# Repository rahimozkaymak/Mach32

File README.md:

# Mach32
An ESP32 based rocket flight computer

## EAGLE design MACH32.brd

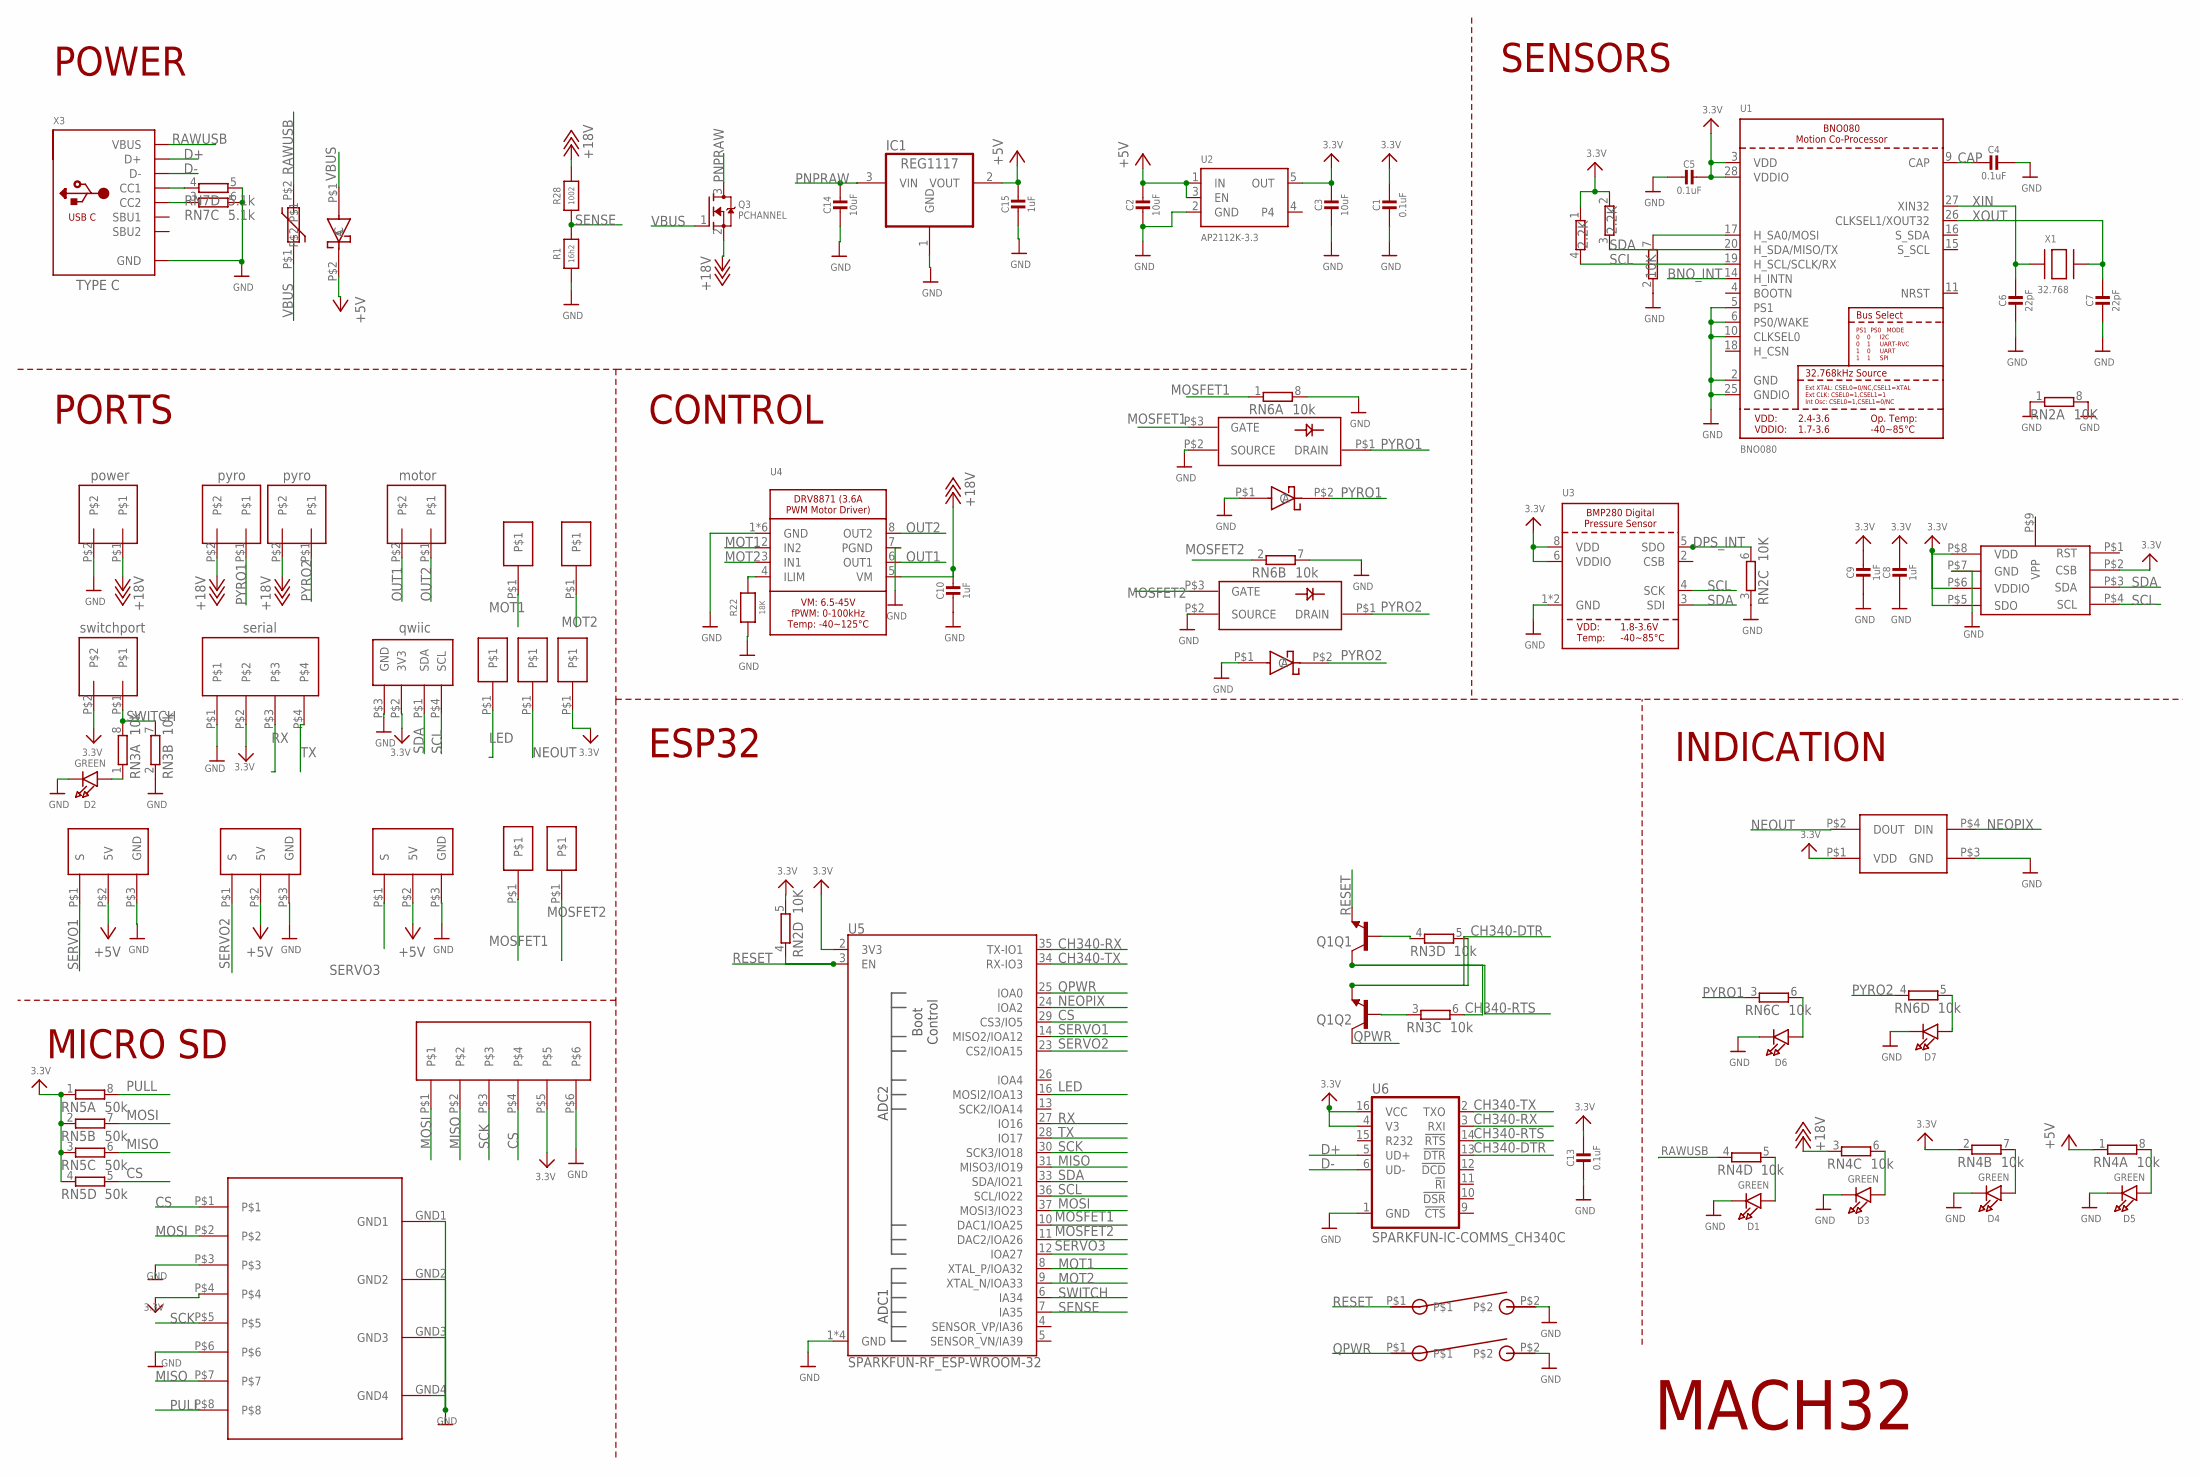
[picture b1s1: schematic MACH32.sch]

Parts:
C1, C4, C5, C13: 0.1uF; 0603-NO
C2, C3, C14: 10uF; 0805-NO
C6, C7: 22pF; 0603-NO
C8, C9, C10, C15: 1uF; 0603-NO
D1, D2, D3, D4, D5, D6, D7: GREEN; CHIPLED_0603_NOOUTLINE
GENERALDIODE, GENERALDIODE2: PG-TSDSON-8-32; BSZ036NE2LSATMA1
IC1: REG1117; SOT223
Q1: SPARKFUN-DISCRETESEMI_TRANS_NPN_DUAL-MBT3904DW1T1; SPARKFUN-DISCRETESEMI_SC70-6
Q3: PCHANNEL; SOT23
R1: 16h2; MICROBUILDER__1206MP
R22: 18K; MICROBUILDER__0603MP
R28: 1002; MICROBUILDER__1206MP
RN1: 2.2K; EXB34V
RN2: 10K; EXB38V
RN3, RN4, RN6: 10k; EXB38V
RN5: 50k; EXB38V
RN7: 5.1k; EXB38V
U1: BNO080
U2: AP2112K-3.3; SOT23-5
U3: BMP280_COMBO; BMX280_COMBO
U4: MICROBUILDER_DRV8871; MICROBUILDER_HSOP8
U5: SPARKFUN-RF_ESP-WROOM-32
U6: SPARKFUN-IC-COMMS_CH340C; SPARKFUN-IC-COMMS_SO016
U$17: 2SMPB-02E; 2021
U$25, U$27, U$28, U$30, U$34: OSTTEXX0104
U$31: DF3-4
U$32: QWIIC; QWIIC_V
U$47: PTC; 1210PTC
U$48, U$49, U$50: SERVO
U$51: SK681-2020; SK6812-2020
U$52, U$53, U$91: SS24FL; XC6220
U$57, U$58, U$59, U$100, U$104, U$105, U$106: MALIPAD
U$67: DF3-6
U$70: ST1W008S4AR1500
U$73, U$74: OMRONSWITCH; BUTTONOMRON
X1: 32.768; XTAL3215
X3: MICROBUILDER_USB_C; MICROBUILDER_USB_C_CUSB31-CFM2AX-01-X

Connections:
3.3V: C1.1, C3.1, C5.1, C8.1, C9.1, C13.1, RN1.1, RN1.2 (1), RN2.5 (2), RN4.2 (1), RN5.1, RN5.2 (1), RN5.3 (1), RN5.4 (1), U1.3 (VDD), U1.28 (VDDIO), U2.5 (OUT), U3.6 (VDDIO), U3.8 (VDD), U5.2 (3V3), U6.4 (V3), U6.16 (VCC), U$17.P$2 (CSB), U$17.P$5 (SDO), U$17.P$6 (VDDIO), U$17.P$8 (VDD), U$31.P$2, U$32.P$2 (3V3), U$34.P$2, U$51.P$1 (VDD), U$57.P$1, U$67.P$5, U$70.P$4
+5V: C2.1, C15.1, IC1.2 (VOUT), RN4.1, U2.1 (IN), U2.3 (EN), U$48.P$2 (5V), U$49.P$2 (5V), U$50.P$2 (5V), U$91.P$2 (C)
+18V: C10.1, Q3.2 (S), R28.2, RN4.3 (1), U4.5 (VM), U$25.P$1, U$27.P$2, U$30.P$2
BNO_INT: U1.14 (H_INTN)
CAP: C4.2, U1.9 (CAP)
CH340-DTR: Q1.1 (E), RN3.5 (2), U6.13 (!DTR)
CH340-RTS: Q1.3 (C), RN3.6 (2), U6.14 (!RTS)
CH340-RX: U5.35 (TX-IO1), U6.3 (RXI)
CH340-TX: U5.34 (RX-IO3), U6.2 (TXO)
CS: RN5.5 (2), U5.29 (CS3/IO5), U$67.P$4, U$70.P$1
D+: U6.5 (UD+), X3.A6 (D+), X3.B6 (D+)
D-: U6.6 (UD-), X3.A7 (D-), X3.B7 (D-)
DPS_INT: RN2.6 (2), U3.5 (SDO)
GND: C1.2, C2.2, C3.2, C4.1, C5.2, C6.2, C7.2, C8.2, C9.2, C10.2, C13.2, C14.2, C15.2, D1.C, D2.C, D3.C, D4.C, D5.C, D6.C, D7.C, GENERALDIODE.P$2 (SOURCE), GENERALDIODE2.P$2 (SOURCE), IC1.1 (GND), R1.1, R22.1, RN2.1, RN2.2 (1), RN2.3 (1), RN2.8 (2), RN3.2 (1), RN6.7 (2), RN6.8 (2), RN7.5 (2), RN7.6 (2), U1.2 (GND), U1.5 (PS1), U1.6 (PS0/WAKE), U1.10 (CLKSEL0), U1.25 (GNDIO), U2.2 (GND), U3.1 (GND), U3.7 (GND), U4.1 (GND), U4.7 (PGND), U4.GND, U4.P$1 (GND), U4.P$2 (GND), U4.P$3 (GND), U4.P$4 (GND), U5.1 (GND), U5.15 (GND), U5.38 (GND), U5.GND, U6.1 (GND), U$17.P$7 (GND), U$25.P$2, U$31.P$1, U$32.P$3 (GND), U$48.P$3 (GND), U$49.P$3 (GND), U$50.P$3 (GND), U$51.P$3 (GND), U$52.P$1 (A), U$53.P$1 (A), U$67.P$6, U$70.GND1, U$70.GND2, U$70.GND3, U$70.GND4, U$70.P$3, U$70.P$6, U$73.P$2, U$74.P$2, X3.A1B12 (GND), X3.B1A12 (GND)
LED: U5.16 (MOSI2/IOA13), U$59.P$1
MISO: RN5.6 (2), U5.31 (MISO3/IO19), U$67.P$2, U$70.P$7
MOSFET1: GENERALDIODE.P$3 (GATE), RN6.1, U5.10 (DAC1/IOA25), U$100.P$1
MOSFET2: GENERALDIODE2.P$3 (GATE), RN6.2 (1), U5.11 (DAC2/IOA26), U$104.P$1
MOSI: RN5.7 (2), U5.37 (MOSI3/IO23), U$67.P$1, U$70.P$2
MOT1: U4.2 (IN2), U5.8 (XTAL_P/IOA32), U$105.P$1
MOT2: U4.3 (IN1), U5.9 (XTAL_N/IOA33), U$106.P$1
unnamed: RN2.7 (2), U1.17 (H_SA0/MOSI)
unnamed: D2.A, RN3.1
unnamed: D1.A, RN4.5 (2)
unnamed: R22.2, U4.4 (ILIM)
unnamed: D3.A, RN4.6 (2)
unnamed: D4.A, RN4.7 (2)
unnamed: D5.A, RN4.8 (2)
unnamed: Q1.5 (B), RN3.4 (1)
unnamed: Q1.2 (B), RN3.3 (1)
unnamed: RN7.4 (1), X3.A5 (CC1)
unnamed: D6.A, RN6.6 (2)
unnamed: D7.A, RN6.5 (2)
unnamed: RN7.3 (1), X3.B5 (CC2)
NEOPIX: U5.24 (IOA2), U$51.P$4 (DIN)
NEOUT: U$51.P$2 (DOUT), U$58.P$1
OUT1: U4.6 (OUT1), U$28.P$2
OUT2: U4.8 (OUT2), U$28.P$1
PNPRAW: C14.1, IC1.3 (VIN), Q3.3 (D)
PULL: RN5.8 (2), U$70.P$8
PYRO1: GENERALDIODE.P$1 (DRAIN), RN6.3 (1), U$27.P$1, U$52.P$2 (C)
PYRO2: GENERALDIODE2.P$1 (DRAIN), RN6.4 (1), U$30.P$1, U$53.P$2 (C)
QPWR: Q1.6 (C), U5.25 (IOA0), U$73.P$1
RAWUSB: RN4.4 (1), U$47.P$2, X3.A4B9 (VBUS), X3.B4A9 (VBUS)
RESET: Q1.4 (E), RN2.4 (1), U5.3 (EN), U$74.P$1
RX: U5.27 (IO16), U$31.P$3
SCK: U5.30 (SCK3/IO18), U$67.P$3, U$70.P$5
SCL: RN1.4 (2), U1.19 (H_SCL/SCLK/RX), U3.4 (SCK), U5.36 (SCL/IO22), U$17.P$4 (SCL), U$32.P$4 (SCL)
SDA: RN1.3 (2), U1.20 (H_SDA/MISO/TX), U3.3 (SDI), U5.33 (SDA/IO21), U$17.P$3 (SDA), U$32.P$1 (SDA)
SENSE: R1.2, R28.1, U5.7 (IA35)
SERVO1: U5.14 (MISO2/IOA12), U$48.P$1 (S)
SERVO2: U5.23 (CS2/IOA15), U$49.P$1 (S)
SERVO3: U5.12 (IOA27), U$50.P$1 (S)
SWITCH: RN3.7 (2), RN3.8 (2), U5.6 (IA34), U$34.P$1
TX: U5.28 (IO17), U$31.P$4
VBUS: Q3.1 (G), U$47.P$1, U$91.P$1 (A)
XIN: C6.1, U1.27 (XIN32), X1.P$1
XOUT: C7.1, U1.26 (CLKSEL1/XOUT32), X1.P$2

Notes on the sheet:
SENSORS
POWER
power
motor
pyro
PORTS
switchport
serial
qwiic
MICRO SD
ESP32
INDICATION
CONTROL
TYPE C
MACH32

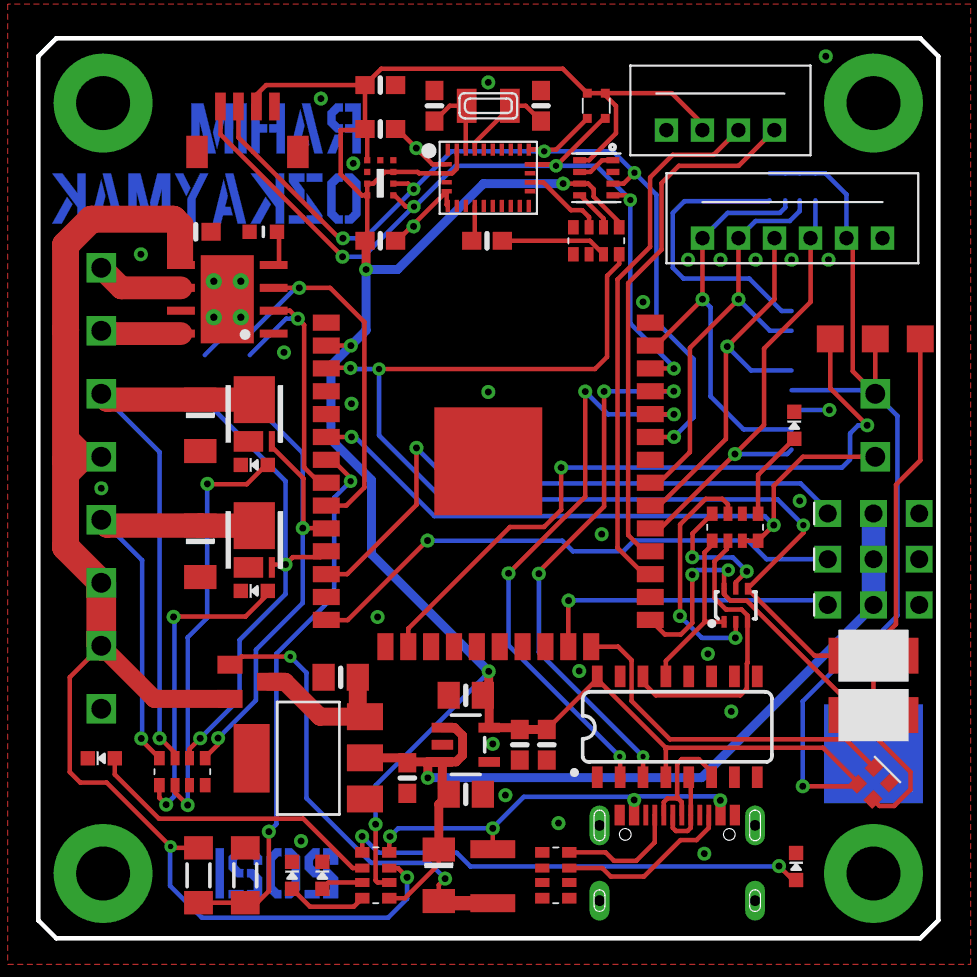
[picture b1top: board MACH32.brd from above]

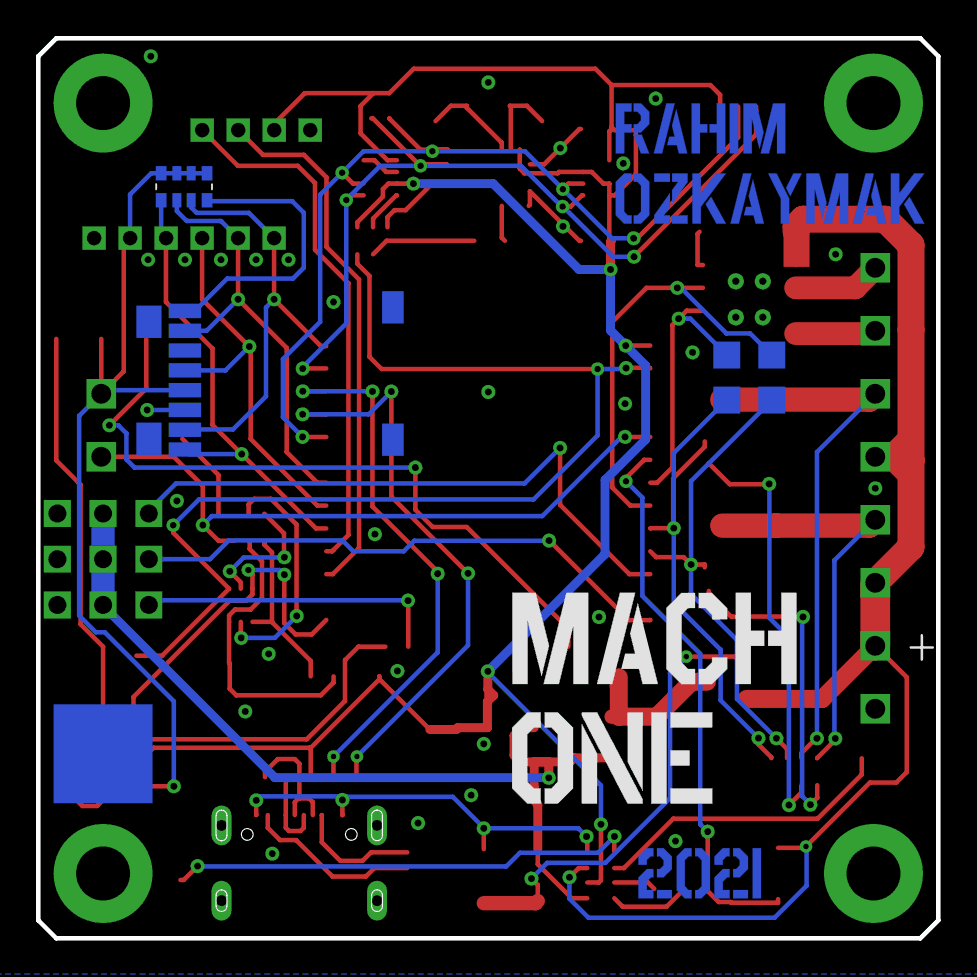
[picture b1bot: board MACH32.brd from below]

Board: 2 copper layers, 50.0 x 50.0 mm, 76 parts (12 on the bottom side), 57 nets.

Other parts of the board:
U$94: OSHW_5MM
U$102: 2021TRUE
U$107: RAHIM
U$108: OZKAYMAK
U$109: A
U$110: ONE

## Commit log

2022-08-31 Create Eagle Files
2022-08-31 Create A

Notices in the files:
parts and their libraries:
microbuilder: This work is placed in the public domain, and may be freely used for commercial and non-commercial work with the following conditions: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
